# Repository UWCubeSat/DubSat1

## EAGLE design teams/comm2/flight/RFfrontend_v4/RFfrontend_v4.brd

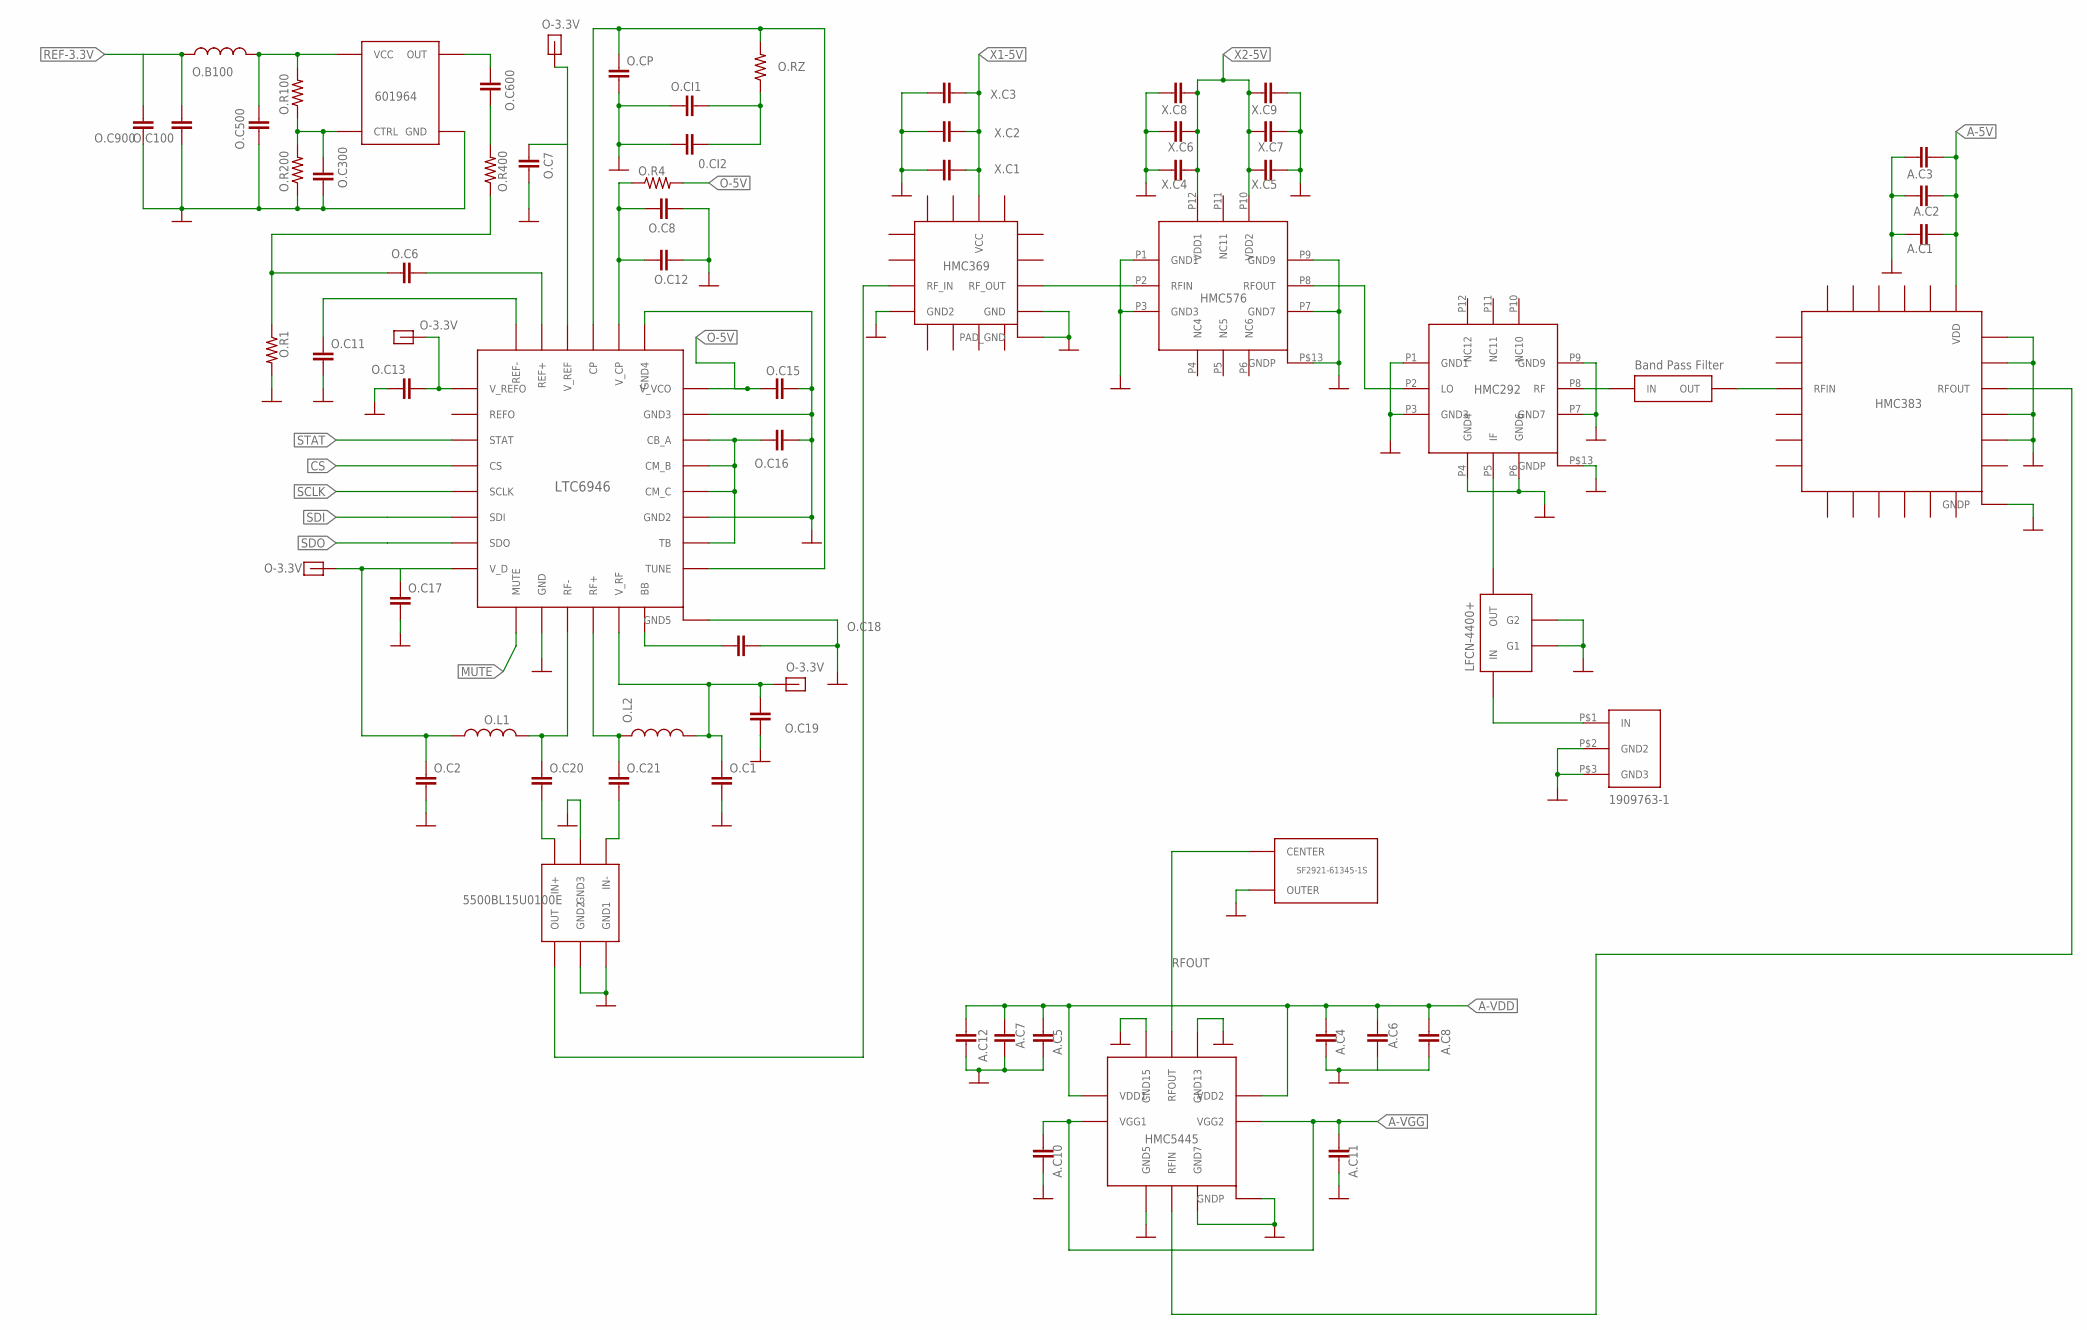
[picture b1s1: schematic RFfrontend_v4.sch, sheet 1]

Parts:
0.CI2: CAP0805; 0805
3.3V: 1PIN_B-T-B_TOPPAD
A.C1, A.C4, A.C5, A.C10, A.C11: CAP0402-CAP; 0402-CAP
A.C2, A.C6, A.C7: CAP0603-CAP; 0603-CAP
A.C3, A.C8, A.C12: CAP0805; 0805
O-3.3V: 1PIN_B-T-B_TOPPAD
O.B100: INDUCTOR0603; 0603
O.C1, O.C2, O.C6, O.C7, O.C11, O.C12, O.C13, O.C15, O.C17, O.C19, O.C20, O.C21: CAP0402-CAP; 0402-CAP
O.C8, O.C16, O.C18: CAP0805; 0805
O.C100, O.C900: CAP1206; 1206
O.C300, O.C500, O.C600, O.CI1, O.CP: CAP0603-CAP; 0603-CAP
O.L1, O.L2: INDUCTOR0402; C0402
O.R1, O.R4: RESISTOR0402-RES; 0402-RES
O.R100, O.R200, O.R400, O.RZ: RESISTOR0603; 0603-RES
U$1: LINEAR_LTC6946; QFN_28PIN
U$9, U$18: 1PIN_B-T-B_TOPPAD
U$13: CRYSTEK_601964; 4_PIN_9X14MM
U$14: HITTITE_HMC369; LP3
U$15: MINICIRCUITS_LPF; FV1206
U$22: HITTITE_HMC576; 12PIN_QFN
U$29: HITTITE_HMC292; 12PIN_QFN
U$39: JOHNSON_5500BL15U0100; 6_PIN_BALUN
U$41: BPF_24GHZ
U$43: HITTITE_HMC383; 24-QFN
U$44: HITTITE_HMC5445; 16PIN_SMT
U$75: SMA_STRAIGHT_SF2921-61345-1S
U$169: TE_UMCC_CONNECTOR; 3_PIN_UMCC
X.C1, X.C4, X.C5: CAP0402-CAP; 0402-CAP
X.C2, X.C6, X.C7: CAP0603-CAP; 0603-CAP
X.C3, X.C8, X.C9: CAP0805; 0805

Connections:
12GHZ: U$14.PIN10 (RF_OUT), U$22.P2 (RFIN)
A-5V: A.C1.2, A.C2.2, A.C3.2, U$43.P$19 (VDD); also elsewhere on the board
A-VDD: A.C4.2, A.C5.2, A.C6.2, A.C7.2, A.C8.2, A.C12.2, U$44.P1 (VDD1), U$44.P11 (VDD2); also elsewhere on the board
A-VGG: A.C10.2, A.C11.2, U$44.P2 (VGG1), U$44.P10 (VGG2); also elsewhere on the board
AGND: 0.CI2.1, A.C1.1, A.C2.1, A.C3.1, A.C4.1, A.C5.1, A.C6.1, A.C7.1, A.C8.1, A.C10.1, A.C11.1, A.C12.1, O.C1.2, O.C2.2, O.C7.1, O.C8.2, O.C11.2, O.C12.2, O.C13.1, O.C15.2, O.C16.2, O.C17.2, O.C18.2, O.C19.1, O.C100.1, O.C300.2, O.C500.2, O.C900.1, O.CI1.1, O.CP.2, O.R1.2, O.R200.1, U$1.P$10 (GND), U$1.P$17 (GND2), U$1.P$21 (GND3), U$1.P$23 (GND4), U$1.P$29 (GND5), U$13.GND, U$14.PAD_GND, U$14.PIN4 (GND2), U$14.PIN9 (GND), U$15.P$1 (G1), U$15.P$2 (G2), U$22.P1 (GND1), U$22.P3 (GND3), U$22.P7 (GND7), U$22.P9 (GND9), U$22.P$13 (GNDP), U$29.P1 (GND1), U$29.P3 (GND3), U$29.P4 (GND4), U$29.P6 (GND6), U$29.P7 (GND7), U$29.P9 (GND9), U$29.P$13 (GNDP), U$39.P$2 (GND2), U$39.P$3 (GND1), U$39.P$5 (GND3), U$43.P$14 (NC14), U$43.P$15 (NC15), U$43.P$17 (NC17), U$43.P$18 (NC18), U$43.P$25 (GNDP), U$44.GNDP, U$44.P5 (GND5), U$44.P7 (GND7), U$44.P13 (GND13), U$44.P15 (GND15), U$75.OUTER, U$169.P$2 (GND2), U$169.P$3 (GND3), X.C1.1, X.C2.1, X.C3.1, X.C4.1, X.C5.2, X.C6.1, X.C7.2, X.C8.1, X.C9.2; also elsewhere on the board
CS: U$1.P$4 (CS); also elsewhere on the board
MUTE: U$1.P$9 (MUTE); also elsewhere on the board
unnamed: O.C8.1, O.C12.1, O.R4.1, U$1.P$24 (V_CP)
unnamed: O.C16.1, U$1.P$16 (TB), U$1.P$18 (CM_C), U$1.P$19 (CM_B), U$1.P$20 (CB_A)
unnamed: O.C20.2, U$39.P$6 (IN+)
unnamed: 0.CI2.2, O.CI1.2, O.RZ.1
unnamed: O.CP.1, O.RZ.2, U$1.P$15 (TUNE), U$1.P$25 (CP)
unnamed: O.C18.1, U$1.P$14 (BB)
unnamed: O.C20.1, O.L1.2, U$1.P$11 (RF-)
unnamed: O.C21.1, O.L2.1, U$1.P$12 (RF+)
unnamed: O.C21.2, U$39.P$4 (IN-)
unnamed: U$14.PIN3 (RF_IN), U$39.P$1 (OUT)
unnamed: O.C11.1, U$1.P$28 (REF-)
unnamed: O.C6.2, U$1.P$27 (REF+)
unnamed: O.C6.1, O.R1.1, O.R400.1
unnamed: O.B100.2, O.C500.1, O.R100.2, U$13.VCC
unnamed: O.C300.1, O.R100.1, O.R200.2, U$13.VCTRL (CTRL)
unnamed: O.C600.1, U$13.OUT
unnamed: U$22.P8 (RFOUT), U$29.P2 (LO)
unnamed: O.C600.2, O.R400.2
unnamed: U$15.P$4 (OUT), U$29.P5 (IF)
unnamed: U$29.P8 (RF), U$41.IN
unnamed: U$41.OUT, U$43.P$3 (RFIN)
unnamed: U$43.P$16 (RFOUT), U$44.P6 (RFIN)
unnamed: U$15.P$3 (IN), U$169.P$1 (IN)
O-3.3V: 3.3V.P$1, O-3.3V.P$1, O.C1.1, O.C2.1, O.C7.2, O.C13.2, O.C17.1, O.C19.2, O.L1.1, O.L2.2, U$1.P$1 (V_REFO), U$1.P$8 (V_D), U$1.P$13 (V_RF), U$1.P$26 (V_REF), U$9.P$1, U$18.P$1; also elsewhere on the board
O-5V: O.C15.1, O.R4.2, U$1.P$22 (V_VCO); also elsewhere on the board
REF-3.3V: O.B100.1, O.C100.2, O.C900.2; also elsewhere on the board
RFOUT: U$44.P14 (RFOUT), U$75.CENTER
SCLK: U$1.P$5 (SCLK); also elsewhere on the board
SDI: U$1.P$6 (SDI); also elsewhere on the board
SDO: U$1.P$7 (SDO); also elsewhere on the board
STAT: U$1.P$3 (STAT); also elsewhere on the board
X1-5V: U$14.PIN14 (VCC), X.C1.2, X.C2.2, X.C3.2; also elsewhere on the board
X2-5V: U$22.P10 (VDD2), U$22.P12 (VDD1), X.C4.2, X.C5.1, X.C6.2, X.C7.1, X.C8.2, X.C9.1; also elsewhere on the board

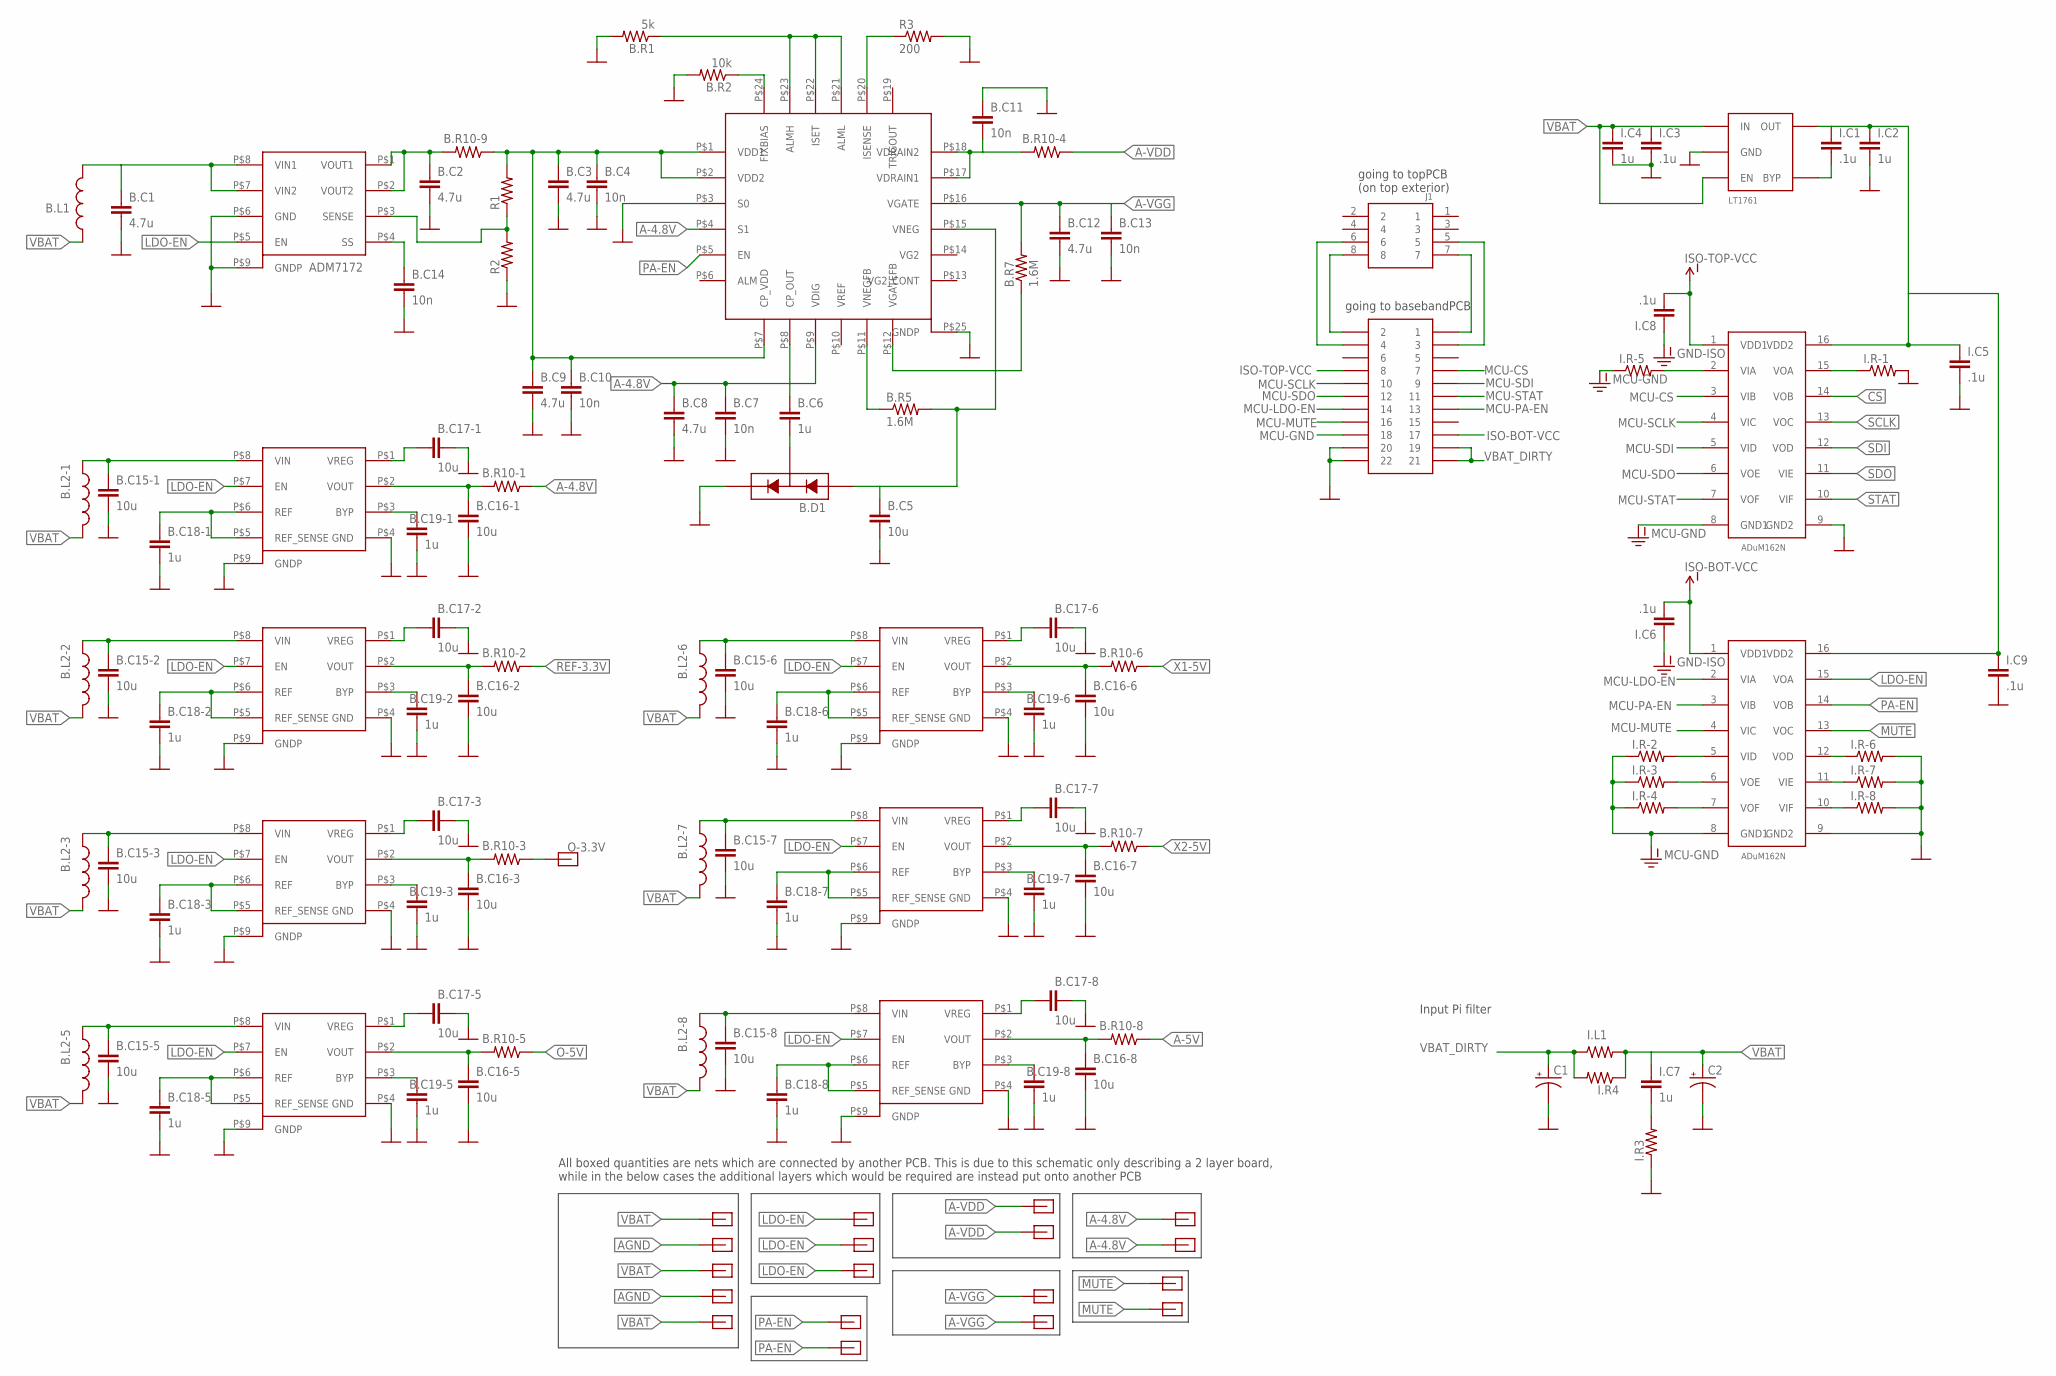
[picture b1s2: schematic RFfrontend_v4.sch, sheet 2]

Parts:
B.C1, B.C2: 4.7u; 1206
B.C3, B.C8, B.C9, B.C12: 4.7u; 0603-CAP
B.C4, B.C7, B.C10, B.C11, B.C13, B.C14: 10n; 0603-CAP
B.C5, B.C15-1, B.C15-2, B.C15-3, B.C15-5, B.C15-6, B.C15-7, B.C15-8, B.C16-1, B.C16-2, B.C16-3, B.C16-5, B.C16-6, B.C16-7, B.C16-8, B.C17-1, B.C17-2, B.C17-3, B.C17-5, B.C17-6, B.C17-7, B.C17-8: 10u; 0805
B.C6, B.C18-1, B.C18-2, B.C18-3, B.C18-5, B.C18-6, B.C18-7, B.C18-8, B.C19-1, B.C19-2, B.C19-3, B.C19-5, B.C19-6, B.C19-7, B.C19-8: 1u; 0805
B.D1: ONSEMI_DIODE_BAT54SL; SOT23-3
B.L1: INDUCTOR0805; 0805
B.L2-1, B.L2-2, B.L2-3, B.L2-5, B.L2-6, B.L2-7, B.L2-8: INDUCTOR0603; 0603
B.R1: 5k; 0603-RES
B.R2: 10k; 0805
B.R5, B.R7: 1.6M; 0805
B.R10-1, B.R10-2, B.R10-3, B.R10-4, B.R10-5, B.R10-6, B.R10-7, B.R10-8, B.R10-9: RESISTOR0805-RES; 0805
C1, C2: CAP_POL7343; EIA7343
I.C1, I.C3, I.C5, I.C6, I.C8, I.C9: .1u; 0402-CAP
I.C2, I.C4, I.C7: 1u; 0805
I.L1: RESISTOR1206; 1206
I.R3, I.R4: RESISTOR0805-RES; 0805
I.R-1, I.R-2, I.R-3, I.R-4, I.R-5, I.R-6, I.R-7, I.R-8: RESISTOR0402-RES; 0402-RES
J1: SLW-104-01-X-D
R1, R2: RESISTOR0805-RES; 0805
R3: 200; 0805
U$19, U$20, U$25, U$26, U$28, U$35, U$36, U$153, U$154, U$155, U$157, U$174, U$175, U$176, U$177, U$189, U$190: 1PIN_B-T-B_TOPPAD
U$51, U$111: ANALOG_ADUM162N0BRZ; SO16
U$61: ANALOG_LDO_ADM7172; 8-LFCSP
U$62: HITTITE_HMC980LP4E; 24-QFN
U$84, U$95, U$103, U$119, U$127, U$135, U$143: ANALOG_LDO_ADM7150; 8-LFCSP
U$113: LINEAR_LDO_LT1761-X; SOT-23-5
U$152, U$156: 1PIN_B-T-B_GROUND
U$180: SSW-111-XX-XXX-D

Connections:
6.3V: B.C3.1, B.C4.1, B.C9.1, B.C10.1, B.R10-9.1, R1.2, U$62.P$1 (VDD1), U$62.P$2 (VDD2), U$62.P$7 (CP_VDD)
A-4.8V: B.C7.1, B.C8.1, B.C16-1.1, B.R10-1.1, B.R10-1.2, U$26.P$1, U$28.P$1, U$62.P$4 (S1), U$62.P$9 (VDIG), U$84.P$2 (VOUT)
A-5V: B.R10-8.1; also elsewhere on the board
A-VDD: B.C11.2, B.R10-4.1, B.R10-4.2, U$62.P$17 (VDRAIN1), U$62.P$18 (VDRAIN2), U$174.P$1, U$175.P$1; also elsewhere on the board
A-VGG: B.C12.1, B.C13.1, B.R7.2, U$62.P$16 (VGATE), U$176.P$1, U$177.P$1; also elsewhere on the board
AGND: B.C1.2, B.C2.2, B.C3.2, B.C4.2, B.C5.2, B.C7.2, B.C8.2, B.C9.2, B.C10.2, B.C11.1, B.C12.2, B.C13.2, B.C14.2, B.C15-1.2, B.C15-2.2, B.C15-3.2, B.C15-5.2, B.C15-6.2, B.C15-7.2, B.C15-8.2, B.C16-1.2, B.C16-2.2, B.C16-3.2, B.C16-5.2, B.C16-6.2, B.C16-7.2, B.C16-8.2, B.C17-1.1, B.C17-2.1, B.C17-3.1, B.C17-5.1, B.C17-6.1, B.C17-7.1, B.C17-8.1, B.C18-1.2, B.C18-2.2, B.C18-3.2, B.C18-5.2, B.C18-6.2, B.C18-7.2, B.C18-8.2, B.C19-1.2, B.C19-2.2, B.C19-3.2, B.C19-5.2, B.C19-6.2, B.C19-7.2, B.C19-8.2, B.D1.2, B.R1.2, B.R2.2, C1.C (-), C2.C (-), I.C2.2, I.C3.2, I.C4.2, I.C5.2, I.C9.2, I.R3.1, I.R-1.2, I.R-6.2, I.R-7.2, I.R-8.2, R2.1, R3.2, U$51.9 (GND2), U$61.P$6 (GND), U$61.P$9 (GNDP), U$62.P$3 (S0), U$62.P$25 (GNDP), U$84.P$4 (GND), U$84.P$9 (GNDP), U$95.P$4 (GND), U$95.P$9 (GNDP), U$103.P$4 (GND), U$103.P$9 (GNDP), U$111.9 (GND2), U$113.P$2 (GND), U$119.P$4 (GND), U$119.P$9 (GNDP), U$127.P$4 (GND), U$127.P$9 (GNDP), U$135.P$4 (GND), U$135.P$9 (GNDP), U$143.P$4 (GND), U$143.P$9 (GNDP), U$152.P$2, U$156.P$2, U$180.20, U$180.22; also elsewhere on the board
CS: U$111.14 (VOB); also elsewhere on the board
ISO-3.3V: I.C1.1, I.C2.1, I.C5.1, I.C9.1, U$51.16 (VDD2), U$111.16 (VDD2), U$113.P$5 (OUT)
ISO-BOT-VCC: I.C6.2, U$51.1 (VDD1), U$180.17
ISO-TOP-VCC: I.C8.2, U$111.1 (VDD1), U$180.8
LDO-EN: U$35.P$1, U$36.P$1, U$51.15 (VOA), U$61.P$5 (EN), U$84.P$7 (EN), U$95.P$7 (EN), U$103.P$7 (EN), U$119.P$7 (EN), U$127.P$7 (EN), U$135.P$7 (EN), U$143.P$7 (EN), U$153.P$1
MCU-CS: U$111.3 (VIB), U$180.7
MCU-GND: I.C6.1, I.C8.1, I.R-2.1, I.R-3.1, I.R-4.1, I.R-5.1, U$51.8 (GND1), U$111.8 (GND1), U$180.18
MCU-LDO-EN: U$51.2 (VIA), U$180.14
MCU-MUTE: U$51.4 (VIC), U$180.16
MCU-PA-EN: U$51.3 (VIB), U$180.13
MCU-SCLK: U$111.4 (VIC), U$180.10
MCU-SDI: U$111.5 (VID), U$180.9
MCU-SDO: U$111.6 (VOE), U$180.12
MCU-STAT: U$111.7 (VOF), U$180.11
MUTE: U$51.13 (VOC), U$189.P$1, U$190.P$1; also elsewhere on the board
unnamed: R1.1, R2.2, U$61.P$3 (SENSE)
unnamed: I.R-1.1, U$111.15 (VOA)
unnamed: R3.1, U$62.P$20 (ISENSE)
unnamed: B.R7.1, U$62.P$12 (VGATEFB)
unnamed: B.C5.1, B.D1.1, B.R5.2, U$62.P$15 (VNEG)
unnamed: B.R5.1, U$62.P$11 (VNEGFB)
unnamed: B.C6.1, U$62.P$8 (CP_OUT)
unnamed: B.C6.2, B.D1.3
unnamed: B.R1.1, U$62.P$21 (ALML), U$62.P$22 (ISET), U$62.P$23 (ALMH)
unnamed: B.R2.1, U$62.P$24 (FIXBIAS)
unnamed: B.C14.1, U$61.P$4 (SS)
unnamed: B.C15-1.1, B.L2-1.1, U$84.P$8 (VIN)
unnamed: B.C17-1.2, U$84.P$1 (VREG)
unnamed: B.C18-1.1, U$84.P$5 (REF_SENSE), U$84.P$6 (REF)
unnamed: B.C15-2.1, B.L2-2.1, U$95.P$8 (VIN)
unnamed: J1.7, U$180.1
unnamed: B.C19-1.1, U$84.P$3 (BYP)
unnamed: B.C18-2.1, U$95.P$5 (REF_SENSE), U$95.P$6 (REF)
unnamed: B.C19-2.1, U$95.P$3 (BYP)
unnamed: B.C16-2.1, B.R10-2.2, U$95.P$2 (VOUT)
unnamed: B.C15-5.1, B.L2-5.1, U$119.P$8 (VIN)
unnamed: B.C15-3.1, B.L2-3.1, U$103.P$8 (VIN)
unnamed: B.C17-3.2, U$103.P$1 (VREG)
unnamed: B.C18-3.1, U$103.P$5 (REF_SENSE), U$103.P$6 (REF)
unnamed: B.C19-3.1, U$103.P$3 (BYP)
unnamed: B.C16-3.1, B.R10-3.2, U$103.P$2 (VOUT)
unnamed: B.C17-5.2, U$119.P$1 (VREG)
unnamed: I.C1.2, U$113.P$4 (BYP)
unnamed: J1.5, U$180.3
unnamed: B.C17-2.2, U$95.P$1 (VREG)
unnamed: B.C18-5.1, U$119.P$5 (REF_SENSE), U$119.P$6 (REF)
unnamed: B.C19-5.1, U$119.P$3 (BYP)
unnamed: B.C16-5.1, B.R10-5.2, U$119.P$2 (VOUT)
unnamed: B.C15-6.1, B.L2-6.1, U$127.P$8 (VIN)
unnamed: B.C17-6.2, U$127.P$1 (VREG)
unnamed: B.C18-6.1, U$127.P$5 (REF_SENSE), U$127.P$6 (REF)
unnamed: I.R-5.2, U$111.2 (VIA)
unnamed: B.C16-6.1, B.R10-6.2, U$127.P$2 (VOUT)
unnamed: B.C15-7.1, B.L2-7.1, U$135.P$8 (VIN)
unnamed: B.C17-7.2, U$135.P$1 (VREG)
unnamed: B.C18-7.1, U$135.P$5 (REF_SENSE), U$135.P$6 (REF)
unnamed: B.C19-7.1, U$135.P$3 (BYP)
unnamed: B.C16-7.1, B.R10-7.2, U$135.P$2 (VOUT)
unnamed: B.C15-8.1, B.L2-8.1, U$143.P$8 (VIN)
unnamed: B.C17-8.2, U$143.P$1 (VREG)
unnamed: B.C18-8.1, U$143.P$5 (REF_SENSE), U$143.P$6 (REF)
unnamed: B.C19-8.1, U$143.P$3 (BYP)
unnamed: B.C16-8.1, B.R10-8.2, U$143.P$2 (VOUT)
unnamed: B.C2.1, B.R10-9.2, U$61.P$1 (VOUT1), U$61.P$2 (VOUT2)
unnamed: I.C7.2, I.R3.2
unnamed: J1.8, U$180.2
unnamed: J1.6, U$180.4
unnamed: I.R-2.2, U$51.5 (VID)
unnamed: I.R-4.2, U$51.7 (VOF)
unnamed: I.R-3.2, U$51.6 (VOE)
unnamed: I.R-6.1, U$51.12 (VOD)
unnamed: I.R-7.1, U$51.11 (VIE)
unnamed: I.R-8.1, U$51.10 (VIF)
unnamed: B.C19-6.1, U$127.P$3 (BYP)
O-3.3V: B.R10-3.1, U$19.P$1; also elsewhere on the board
O-5V: B.R10-5.1; also elsewhere on the board
PA-EN: U$51.14 (VOB), U$62.P$5 (EN), U$154.P$1, U$157.P$1
REF-3.3V: B.R10-2.1; also elsewhere on the board
SCLK: U$111.13 (VOC); also elsewhere on the board
SDI: U$111.12 (VOD); also elsewhere on the board
SDO: U$111.11 (VIE); also elsewhere on the board
STAT: U$111.10 (VIF); also elsewhere on the board
VBAT: B.L1.1, B.L2-1.2, B.L2-2.2, B.L2-3.2, B.L2-5.2, B.L2-6.2, B.L2-7.2, B.L2-8.2, C2.A (+), I.C3.1, I.C4.1, I.C7.1, I.L1.2, I.R4.1, U$20.P$1, U$25.P$1, U$113.P$1 (IN), U$113.P$3 (EN), U$155.P$1
VBAT_DIRTY: C1.A (+), I.L1.1, I.R4.2, U$180.19, U$180.21
VIN: B.C1.1, B.L1.2, U$61.P$7 (VIN2), U$61.P$8 (VIN1)
X1-5V: B.R10-6.1; also elsewhere on the board
X2-5V: B.R10-7.1; also elsewhere on the board

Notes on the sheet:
Input Pi filter
All boxed quantities are nets which are connected by another PCB. This is due to this schematic only describing a 2 layer board, while in the below cases the additional layers which would be required are instead put onto another PCB
going to basebandPCB
going to topPCB (on top exterior)

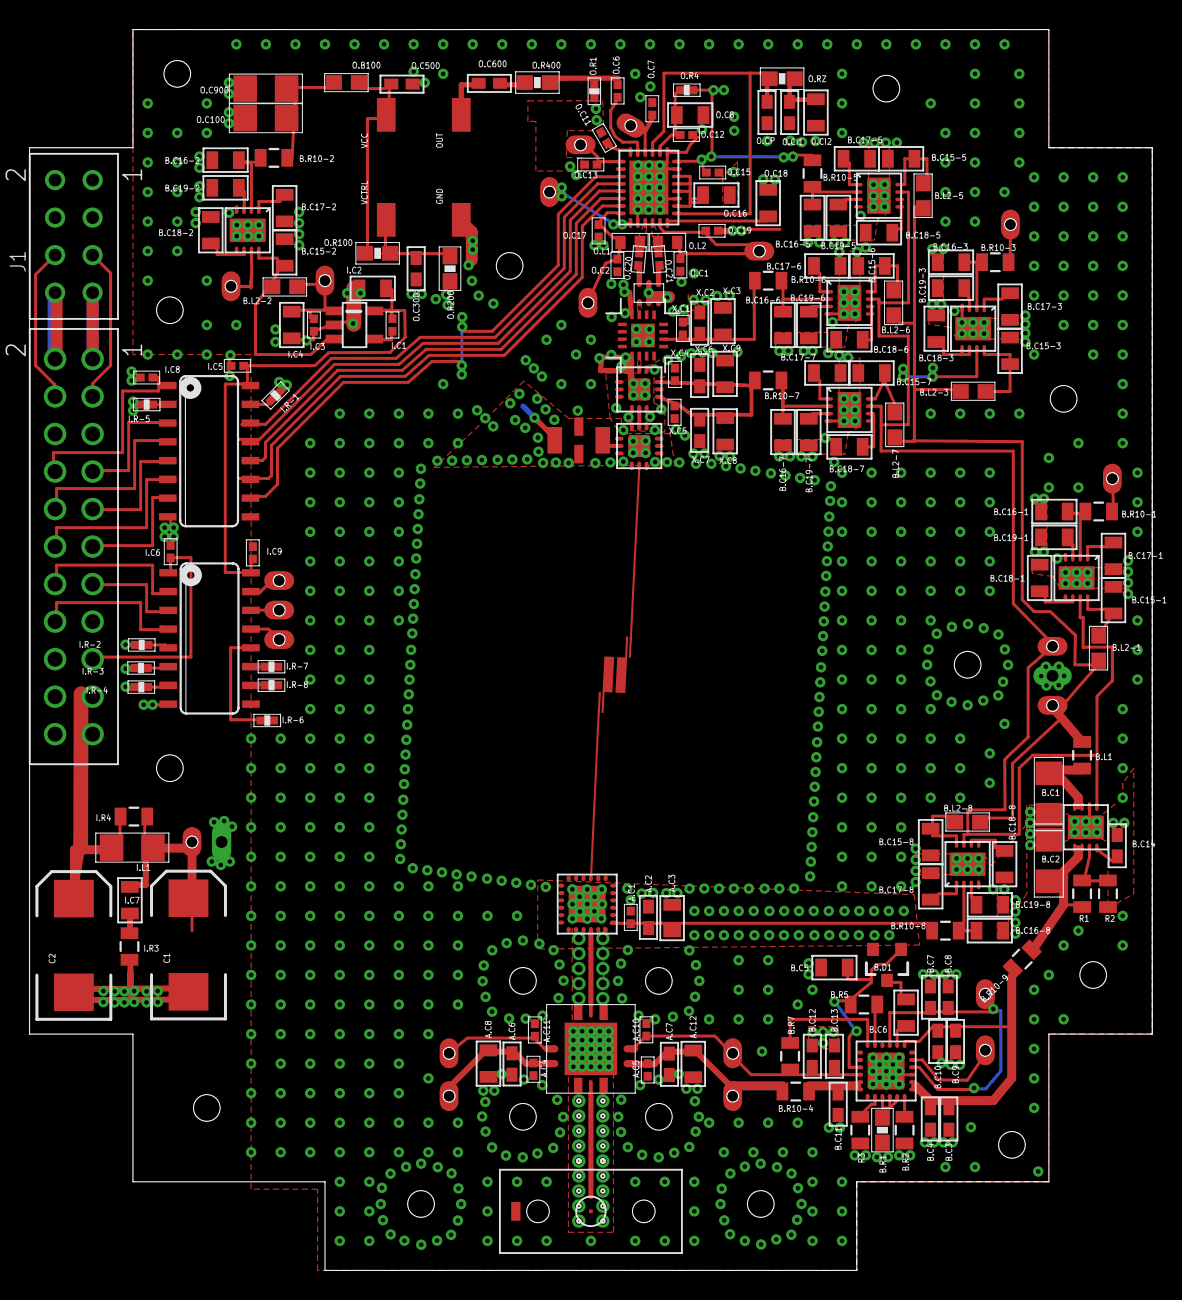
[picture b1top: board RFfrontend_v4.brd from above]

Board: 3 copper layers, 76.0 x 84.0 mm, 216 parts (1 on the bottom side), 118 nets.

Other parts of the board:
U$45, U$158, U$159, U$160, U$161, U$162, U$163, U$164, U$165, U$166, U$167, U$170, U$171, U$172, U$173, U$178: #1-72_BOLT_HOLE
U$151: RF_FRONT_END_OUTLINE_V1
U$191, U$192: CPW_VIA_GUIDE

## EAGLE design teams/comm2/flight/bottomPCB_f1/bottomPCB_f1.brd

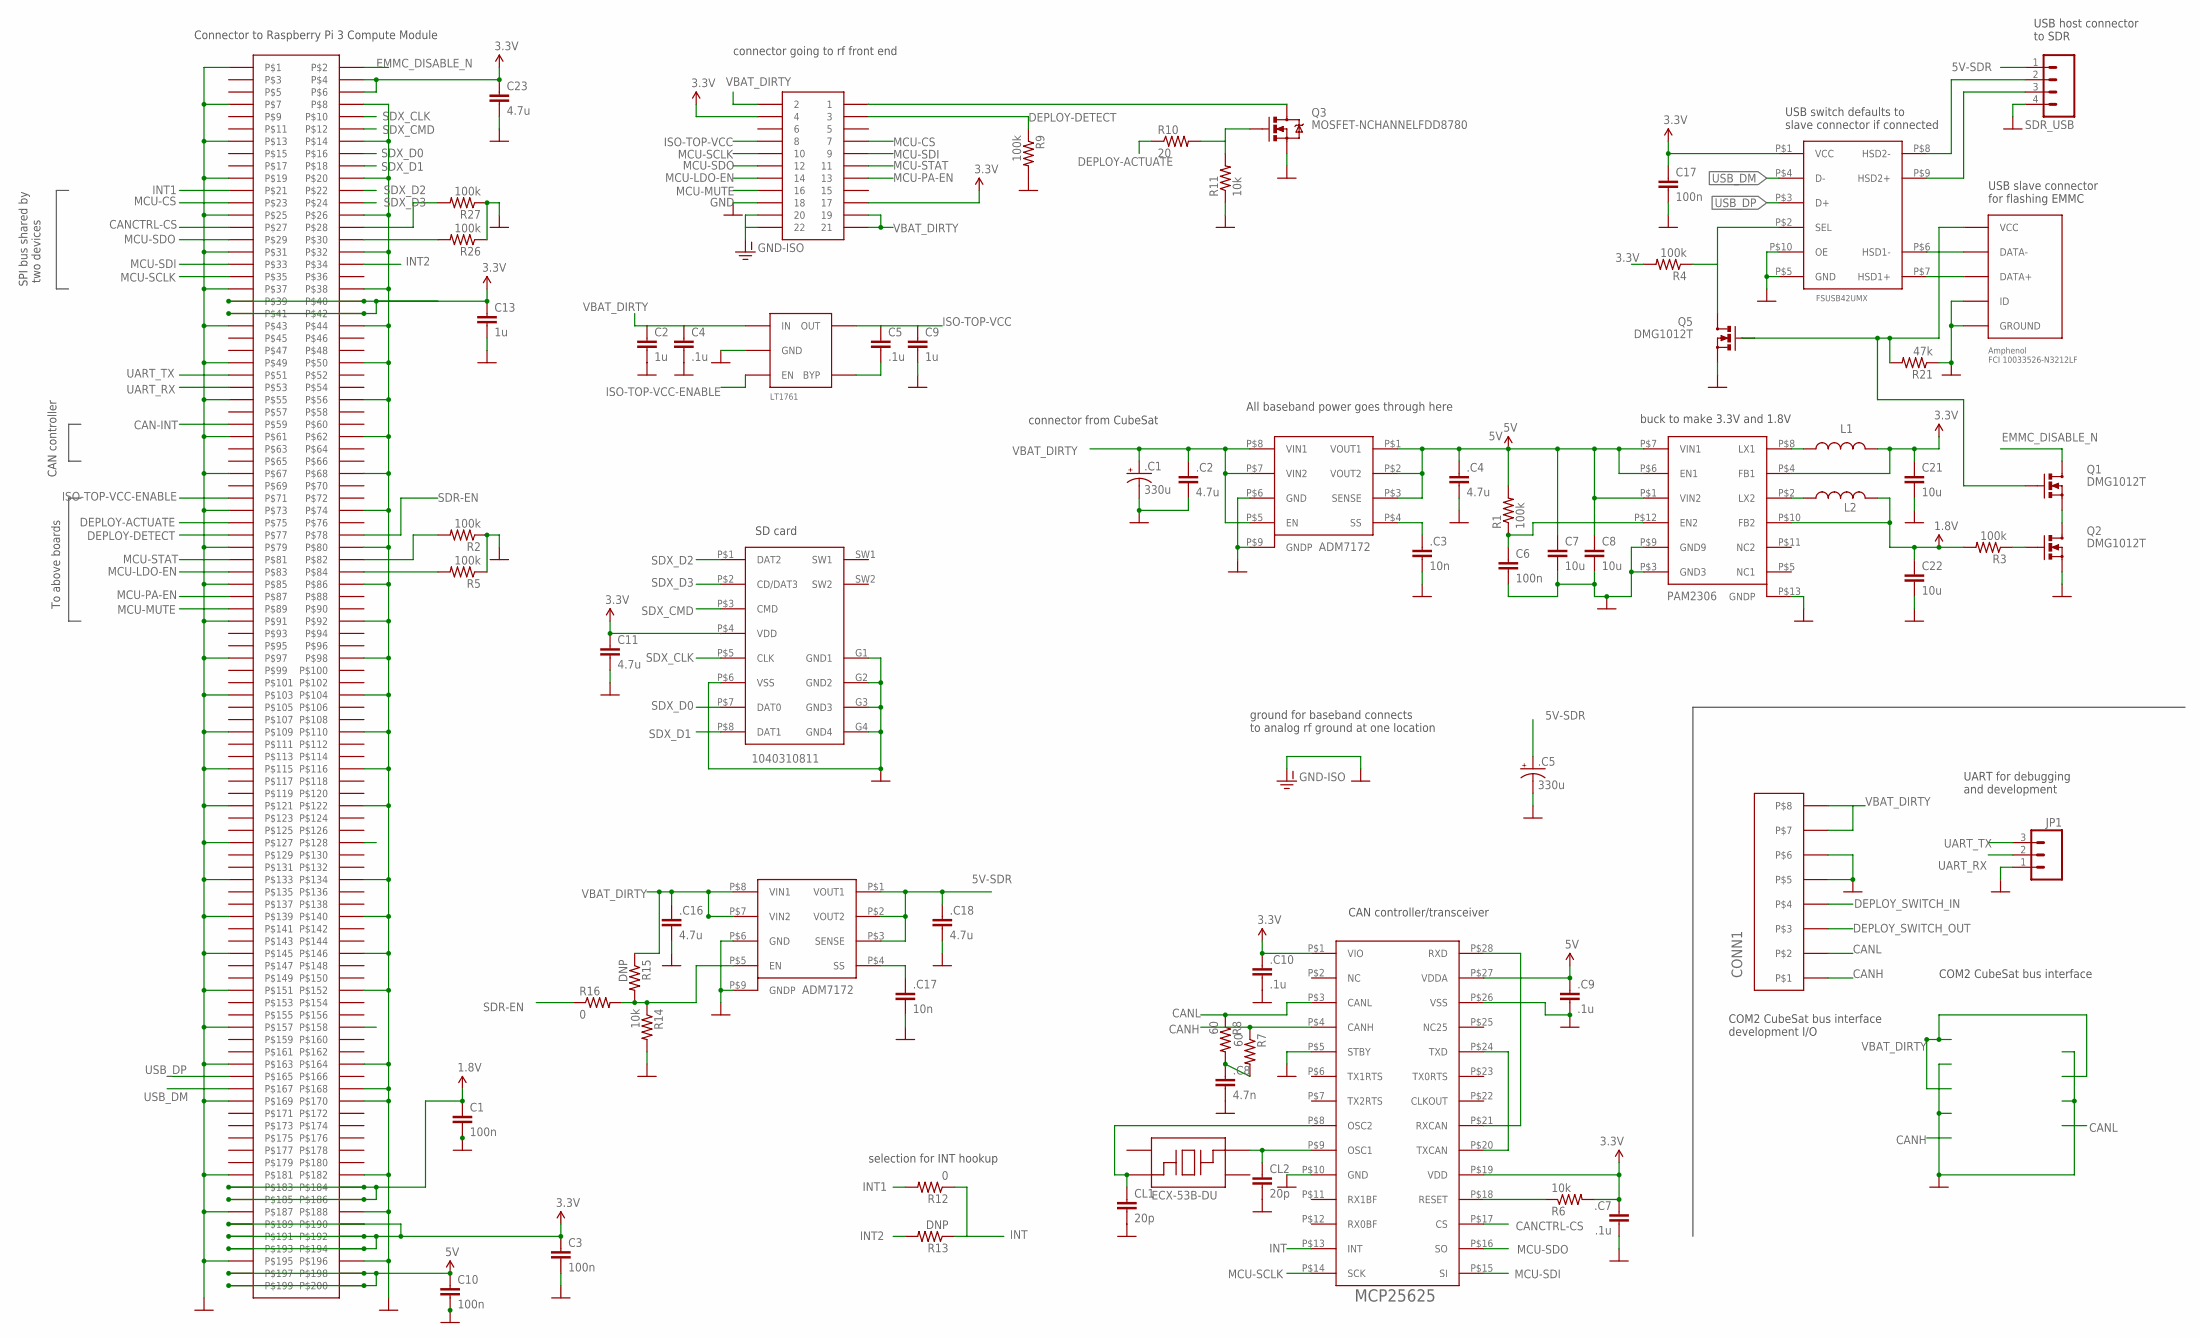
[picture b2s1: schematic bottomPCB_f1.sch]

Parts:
.C1, .C5: 330u; EIA7343
.C2, .C4, .C16, .C18: 4.7u; 1206
.C3, .C17: 10n; 0805
.C7, .C9, .C10: .1u; 0805
.C8: 4.7n; 0805
C1, C3, C6, C10, C17: 100n; 0805
C2, C9, C13: 1u; 0805
C4, C5: .1u; 0805
C7, C8, C21, C22: 10u; 1206
C11, C23: 4.7u; 0805
CL1, CL2: 20p; 0805
CONN1: PICOLOCK_8PICOLOCK_8; PICOLOCK_8
JP1: M03LOCK; 1X03_LOCK
L1, L2: INDUCTOR_SRN4018; SDR0403
Q1, Q2, Q5: DMG1012T; SOT523
Q3: MOSFET-NCHANNELFDD8780; DPAK
R1, R2, R3, R4, R5, R9, R26, R27: 100k; 0805
R6, R11, R14: 10k; 0805
R7, R8: 60; 0805
R10: 20; 0805
R12, R16: 0; 0805
R13, R15: DNP; 0805
R21: 47k; 0805
SDR_USB: M04LOCK; 1X04_LOCK
U$15: USB_MINI-B_AMPHENOL; USB_MINI_B
U$16, U$26: ANALOG_LDO_ADM7172; 8-LFCSP
U$17: DIDOESINCORPORATED_BUCK_PAM2306; WDFN-12L
U$18: MICROCHIP_CAN_MCP25625_SSOP; SSOP-28
U$19: FAIRCHILD_USB_FSUSB42UMX; MSOP_10_LEAD
U$20: LINEAR_LDO_LT1761-X; SOT-23-5
U$21: DDR2_AMPHENOL_10033853-052FSLF; DDR2
U$22: SD_CARD_1040310811
U$24: ECS_CRYSTAL_ECX-53B-DU; SMD_CRYSTAL
U$180: SSW-111-XX-XXX-D

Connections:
1.8V: C1.1, C22.1, L2.P$2 (2), R3.2, U$17.P$10 (FB2), U$21.P$183, U$21.P$184, U$21.P$185, U$21.P$186
3.3V: .C7.1, .C10.1, C3.1, C11.1, C13.1, C17.1, C21.1, C23.1, L1.P$2 (2), R4.2, R6.2, U$17.P$4 (FB1), U$18.P$1 (VIO), U$18.P$19 (VDD), U$19.P$1 (VCC), U$21.P$4, U$21.P$6, U$21.P$39, U$21.P$40, U$21.P$41, U$21.P$42, U$21.P$189, U$21.P$190, U$21.P$191, U$21.P$192, U$21.P$193, U$21.P$194, U$22.P$4 (VDD), U$180.4, U$180.17
5V: .C4.1, .C9.1, C7.1, C8.1, C10.1, R1.2, U$16.P$1 (VOUT1), U$16.P$2 (VOUT2), U$16.P$3 (SENSE), U$17.P$1 (VIN2), U$17.P$6 (EN1), U$17.P$7 (VIN1), U$18.P$27 (VDDA), U$21.P$197, U$21.P$198, U$21.P$199, U$21.P$200
5V-SDR: .C5.A (+), .C18.1, SDR_USB.1, U$26.P$1 (VOUT1), U$26.P$2 (VOUT2), U$26.P$3 (SENSE)
CAN-INT: U$21.P$59
CANCTRL-CS: U$18.P$17 (CS), U$21.P$27
CANH: CONN1.P$1, R7.1, U$18.P$4 (CANH)
CANL: CONN1.P$2, R8.1, U$18.P$3 (CANL)
DEPLOY-ACTUATE: R10.1, U$21.P$75
DEPLOY-DETECT: R9.1, U$21.P$77, U$180.3
DEPLOY_NEG: Q3.4 (D), U$180.1
DEPLOY_SWITCH_IN: CONN1.P$4
DEPLOY_SWITCH_OUT: CONN1.P$3
EMMC_DISABLE_N: Q1.D, U$21.P$2
EN: R14.1, R15.2, R16.2, U$26.P$5 (EN)
GND: .C1.C (-), .C2.2, .C3.2, .C4.2, .C5.C (-), .C7.2, .C8.2, .C9.2, .C10.2, .C16.2, .C17.2, .C18.2, C1.2, C2.2, C3.2, C4.2, C6.2, C7.2, C8.2, C9.2, C10.2, C11.2, C13.2, C17.2, C21.2, C22.2, C23.2, CL1.2, CL2.2, CONN1.P$5, CONN1.P$6, JP1.1, Q2.S, Q3.3 (S), Q5.S, R2.1, R5.1, R9.2, R11.1, R14.2, R21.1, R26.1, R27.1, SDR_USB.4, U$15.GND1 (GROUND), U$15.GND2 (GROUND), U$15.GND3 (GROUND), U$15.GND4 (GROUND), U$15.GROUND, U$15.ID, U$16.P$6 (GND), U$16.P$9 (GNDP), U$17.P$3 (GND3), U$17.P$9 (GND9), U$17.P$13 (GNDP), U$18.P$5 (STBY), U$18.P$10 (GND), U$18.P$26 (VSS), U$19.P$5 (GND), U$19.P$10 (OE), U$20.P$2 (GND), U$21.P$1, U$21.P$7, U$21.P$8, U$21.P$13, U$21.P$14, U$21.P$19, U$21.P$20, U$21.P$25, U$21.P$26, U$21.P$31, U$21.P$32, U$21.P$37, U$21.P$38, U$21.P$43, U$21.P$44, U$21.P$49, U$21.P$50, U$21.P$55, U$21.P$56, U$21.P$61, U$21.P$62, U$21.P$67, U$21.P$68, U$21.P$73, U$21.P$74, U$21.P$79, U$21.P$80, U$21.P$85, U$21.P$86, U$21.P$91, U$21.P$92, U$21.P$97, U$21.P$98, U$21.P$103, U$21.P$104, U$21.P$109, U$21.P$110, U$21.P$115, U$21.P$116, U$21.P$121, U$21.P$122, U$21.P$127, U$21.P$133, U$21.P$134, U$21.P$139, U$21.P$140, U$21.P$145, U$21.P$146, U$21.P$151, U$21.P$152, U$21.P$157, U$21.P$163, U$21.P$164, U$21.P$168, U$21.P$169, U$21.P$170, U$21.P$181, U$21.P$182, U$21.P$187, U$21.P$188, U$21.P$195, U$21.P$196, U$22.G1 (GND1), U$22.G2 (GND2), U$22.G3 (GND3), U$22.G4 (GND4), U$22.P$6 (VSS), U$26.P$6 (GND), U$26.P$9 (GNDP), U$180.18, U$180.20, U$180.22
INT: R12.1, R13.1, U$18.P$13 (INT)
INT1: R12.2, U$21.P$21
INT2: R13.2, U$21.P$34
ISO-TOP-VCC: C5.1, C9.1, U$20.P$5 (OUT), U$180.8
ISO-TOP-VCC-ENABLE: U$20.P$3 (EN), U$21.P$71
MCU-CS: U$21.P$23, U$180.7
MCU-LDO-EN: U$21.P$83, U$180.14
MCU-MUTE: U$21.P$89, U$180.16
MCU-PA-EN: U$21.P$87, U$180.13
MCU-SCLK: U$18.P$14 (SCK), U$21.P$35, U$180.10
MCU-SDI: U$18.P$15 (SI), U$21.P$33, U$180.9
MCU-SDO: U$18.P$16 (SO), U$21.P$29, U$180.12
MCU-STAT: U$21.P$81, U$180.11
unnamed: L1.P$1 (1), U$17.P$8 (LX1)
unnamed: .C3.1, U$16.P$4 (SS)
unnamed: Q1.S, Q2.D
unnamed: L2.P$1 (1), U$17.P$2 (LX2)
unnamed: C6.1, R1.1, U$17.P$12 (EN2)
unnamed: R27.2, U$21.P$28
unnamed: R26.2, U$21.P$30
unnamed: U$15.DATA-, U$19.P$6 (HSD1-)
unnamed: U$15.DATA+, U$19.P$7 (HSD1+)
unnamed: SDR_USB.2, U$19.P$8 (HSD2-)
unnamed: SDR_USB.3, U$19.P$9 (HSD2+)
unnamed: Q5.D, R4.1, U$19.P$2 (SEL)
unnamed: R2.2, U$21.P$82
unnamed: R5.2, U$21.P$84
unnamed: C5.2, U$20.P$4 (BYP)
unnamed: R6.1, U$18.P$18 (RESET)
unnamed: U$18.P$20 (TXCAN), U$18.P$24 (TXD)
unnamed: .C8.1, R7.2, R8.2
unnamed: CL2.1, U$18.P$9 (OSC1), U$24.P$3
unnamed: CL1.1, U$18.P$8 (OSC2), U$24.P$1
unnamed: U$18.P$21 (RXCAN), U$18.P$28 (RXD)
unnamed: Q3.1 (G), R10.2, R11.2
unnamed: .C17.1, U$26.P$4 (SS)
Q2: Q2.G, R3.1
SDR-EN: R16.1, U$21.P$78
SDX_CLK: U$21.P$10, U$22.P$5 (CLK)
SDX_CMD: U$21.P$12, U$22.P$3 (CMD)
SDX_D0: U$21.P$16, U$22.P$7 (DAT0)
SDX_D1: U$21.P$18, U$22.P$8 (DAT1)
SDX_D2: U$21.P$22, U$22.P$1 (DAT2)
SDX_D3: U$21.P$24, U$22.P$2 (CD/DAT3)
UART_RX: JP1.2, U$21.P$53
UART_TX: JP1.3, U$21.P$51
USB_DM: U$19.P$4 (D-), U$21.P$167
USB_DP: U$19.P$3 (D+), U$21.P$165
VBAT_DIRTY: .C1.A (+), .C2.1, .C16.1, C2.1, C4.1, CONN1.P$7, CONN1.P$8, R15.1, U$16.P$5 (EN), U$16.P$7 (VIN2), U$16.P$8 (VIN1), U$20.P$1 (IN), U$26.P$7 (VIN2), U$26.P$8 (VIN1), U$180.2, U$180.19, U$180.21
VBUSB: Q1.G, Q5.G, R21.2, U$15.VCC

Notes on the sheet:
ground for baseband connects to analog rf ground at one location
connector going to rf front end
connector from CubeSat
All baseband power goes through here
buck to make 3.3V and 1.8V
USB switch defaults to slave connector if connected
USB slave connector for flashing EMMC
USB host connector to SDR
Connector to Raspberry Pi 3 Compute Module
UART for debugging and development
SPI bus shared by two devices
To above boards
COM2 CubeSat bus interface
CAN controller
COM2 CubeSat bus interface development I/O
CAN controller/transceiver
SD card
selection for INT hookup

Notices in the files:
parts and their libraries:
SparkFun-Capacitors: Licensing: Creative Commons ShareAlike 4.0 International - https://creativecommons.org/licenses/by-sa/4.0
